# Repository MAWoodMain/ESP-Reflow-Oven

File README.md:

<!--
*** Thanks for checking out the Best-README-Template. If you have a suggestion
*** that would make this better, please fork the repo and create a pull request
*** or simply open an issue with the tag "enhancement".
*** Thanks again! Now go create something AMAZING! :D
***
***
***
*** To avoid retyping too much info. Do a search and replace for the following:
*** github_username, repo_name, twitter_handle, email, project_title, project_description
-->

<!--
*** This readme is based on the template from this github project
*** https://github.com/othneildrew/Best-README-Template
-->

<!-- PROJECT SHIELDS -->
<!--
*** I'm using markdown "reference style" links for readability.
*** Reference links are enclosed in brackets [ ] instead of parentheses ( ).
*** See the bottom of this document for the declaration of the reference variables
*** for contributors-url, forks-url, etc. This is an optional, concise syntax you may use.
*** https://www.markdownguide.org/basic-syntax/#reference-style-links
-->

<br />
<p align="center">

  <h3 align="center">ESP Reflow Oven</h3>

  <p align="center">
    A retro fit of a Lidl middle aisle mini oven into a home reflow oven
  </p>
</p>

<!-- TABLE OF CONTENTS -->
<details open="open">
  <summary><h2 style="display: inline-block">Table of Contents</h2></summary>
  <ol>
    <li>
      <a href="#about-the-project">About The Project</a>
      <ul>
        <li><a href="#objectives">Objectives</a></li>
        <li><a href="#component-selection">Component Selection</a></li>
      </ul>
    </li>
    <li>
      <a href="#the-build">The Build</a>
      <ul>
        <li><a href="#components">Components</a></li>
        <li><a href="#assembly">Assembly</a></li>
      </ul>
    </li>
    <li><a href="#the-final-product">The Final Product</a></li>
    <li><a href="#reflections">Reflections</a></li>
    <li><a href="#license">License</a></li>
  </ol>
</details>

<!-- ABOUT THE PROJECT -->
## About The Project
This project came about on a friday night trip to lidl in the UKs second lockdown. I spotted that lidl were selling mini ovens in the middle aisle for a meagre £25 (~$35), having seen many online creators doing their own homemade reflow ovens based on similar toaster ovens I though it would be a worthy weekend project.  
Naturally after getting home from lidl and putting away all the chilled and frozen foods I went straight into a teardown to see how this thing was put together, the original oven had 3 dials on the front:
* Temperature
* Mode (top/bottom/both elements)
* Timer

Under the hood there was practically nothing just a large void in the case with a few wires going to the elements, the temperature control was a simple bimetallic strip temeperature control which seems to operate based on the temperature in the chamber next to the oven? Not sure how that could even work properly, either way its going into the bin. Similar story for the mode switch, it just switches in and out elements based on the selection, this will not be required either.

After they were removed I was left with the mains input going through a thermal fuse and into a timer switch, I will keep the timer switch to I can set an automatic off when using the unit under computer control. Also this timer switch makes a rather satisfying ding sound when it turns off, I would hate to lose such an important feature...

<!-- OBJECTIVES -->
### Objectives
Had only a few key objectives when I started this project:

* All the mechanical components should be 3D printable using FDM technology.

* I wanted to utilise ESPHome as I have been following some creators project using it, and I was keen to give it a go.

* I wanted the SMT components on the PCB to be assembled by JLC assembly, I know this one sounds a bit weird given I am constructing a reflow oven, but it honestly is often cheaper to have components assembled at JLCPCB rather than ordering them, paying shipping for both PCBs and components then organising paste and a stencil. This oven if for when I have to use components not available for this service and for special cases.

* I needed the oven to follow a simple reflow curve, doesn't need to be prefect but it must work for basic board with normal components.

* I also wanted to try out a Nextion display as I had also seen a few videos by [Vaclav Chaloupka](https://www.youtube.com/user/bruxy70) making some cool home assistant home control panels using the modules.

* Finally I wanted to keep all the original products safety features in place so I don't create a major fire hazard.

<!-- COMPONENT SELECTION -->
### Component Selection

I knew this project would involve working with mains electricity so I made sure to choose components with recognisable approvals and safety certifications for the mains side of the electronics. For that reason I chose a [meanwell isolated AC to DC converter](https://www.meanwell.com/Upload/PDF/IRM-05/IRM-05-SPEC.PDF) to power the low voltage side of the electronics.

The heating elements were tested and found to draw around 600 Watts each which in the UK is around 2.5-3 Amps, the switching component selected for this load was a 5 Amp solid state relay. Specifically I made sure to select a zero crossing SSR as with resistive loads it is better for the powerline quality in the house as it avoids harsh mid phase loading. A [CX240D5](http://www.crydom.com/en/products/catalog/cx-series-ac-pcb-mount.pdf) was used as it was easily available and has approvals several reputable approvals (UL, CSA and CE).

A supplementary on board fuse holder and fuse was included in the design just in case the plug fuse is especially slow or overrated.

The low voltage side will be an ESP32, some thermocouple inputs and a DC output to allow for a fan in the future if required to cool the electronics.

For the thermocouple inputs I have very few ICs to choose from as JLC Assembly did not seem to have many available, I settled on the [MAX31855](https://datasheets.maximintegrated.com/en/ds/MAX31855.pdf) which includes cold junction compensation and requires no external components to work aside from basic decoupling. It uses SPI to send data back to the MCU, it has no settings to configure and does not support receiving data over SPI.

The fan output is a 5V power output which consists of a P-Channel MOSFET and a NPN drive transistor for the gate. This output can only support about 0.5A output as the meanwell power supply is only rated for 1A and the ESP32 required 0.5A.

Below is the 3D model of the PCB in the Kicad 3D viewer:

<!-- THE BUILD -->
## The Build

<!-- COMPONENTS -->
### Components

In addition to the assembled PCB discussed above and the 3D printed parts, a few extra components are required:
* 1 x u.FL to SMA pig tail to allow for an external antenna for the WiFi.
* 1 x SMA 2.4 GHz antenna
* 1 x USB to UART module (3.3V logic) to program the ESP and Nextion display
* 1x Nextion NX4832K035 display module
* 1x Custom cable to connect the nextion display to the PCB (JST-PH)
* 2x bead K type thermocouples
* Optional 1x high mass K type thermocouple for chamber air temperature

<!-- ASSEMBLY -->
### Assembly
The PCBs arrived SMT complete from JLCPCB, the THT components were hand soldered in to finish the PCBA off.
At this point it is worth getting the firmware uploaded into the ESP32, after the first firmware is loaded OTA updating is trivial using the ESPHome home assistant plugin.

It is also worth preparing the Nextion display module, I uploaded the firmware to the display using a USB to UART module and the nextion editor software.

As discussed in the project intro the original mode and temperature knobs were removed. 
Next some stand offs were mounted in the space next to the heating chamber to affix the PCB to.
The PCB was mounted and custom cables were crimped to connect up the mains input and heating elements.
Some holes were drilled to allow the thermocouples into the heated chamber one on the top of the right side and one on the bottom.

A hole was drilled for the SMA connector on the top and the u.FL end was plugged into the ESP32 module.

Next the 3D printed LCD mount was screwed into the front panel using the original self tapping screws which held the old controls on. The LCD was itself screwed into the mount using M3x10mm pan head bolts and the cable was run back to the main PCB. The LCD cover was pressed on to finish off the front. I discovered you must take care pressing this cover on as if you press it on too far it triggers the resistive touch screen on the nextion module.

Below is a photo of the electronics compartment, please don't judge the wire runs too heavily as it has been improved since.

Once the assembly was complete the PIDs loops require tuning so I attached the top and bottom thermocouples to a blank PCB and ran the auto tune routine for both the top and bottom PID control loops.
These values were saved into the ESPHome YAML so they persist though reboot.

<!-- THE FINAL PRODUCT -->
## The Final Product

<!-- REFLECTIONS -->
## Reflections

I am happy with the final product I think the outside looks very clean and the interface is simple and intuitive.
There are a few issues I ran into during this project:
* Two PID loops, since I went with independent top and bottom heat controls I have two PID loops for the top and bottom systems but since these two systems are used simultaneously they are not independent closed loop systems. The issue with this is that the PID settings do not account properly the other loop existing and thus tend to overshoot the set temperature when they are used together. For reflow I have not found a 5 degree overshoot to be a problem but for some use cases I could see it being an issue. I would propose two possible solutions: You could either combine the two elements and control them as a single large element in a single PID loop or you could use a more sophisticated control system which accounted for the second elements influence.

* Dependence on Home assistant, in the way I am currently controlling it the oven relys on HASS to orchastrate the reflow cycle, if the connection to HASS is lost the oven could be left on at the set temperature for too long. Also it means if HASS is unavailable the cycle button does not work properly. This could be resolved by hard coding the cycle into the ESPHome config, but I have not done this yet.

* Cost, this project was started because of the cheapness of the oven but untimately its cost mostly came in the PCBA price. The total price of the PCB was around £17 for the PCBs from JLC (part assembled) and around £35 of THT parts from Farnell for a total cost of £52 (parts) + £25 (oven) = £77 (~$105). I don't feel I over spent given the capability of this oven but it is slightly more then I though it would cost. The main cost issue was in the farnell parts but this was caused by the safe main voltage components, so it is likely unavoidable.

<!-- LICENSE -->
## License

Distributed under the MIT License. See `LICENSE` for more information.

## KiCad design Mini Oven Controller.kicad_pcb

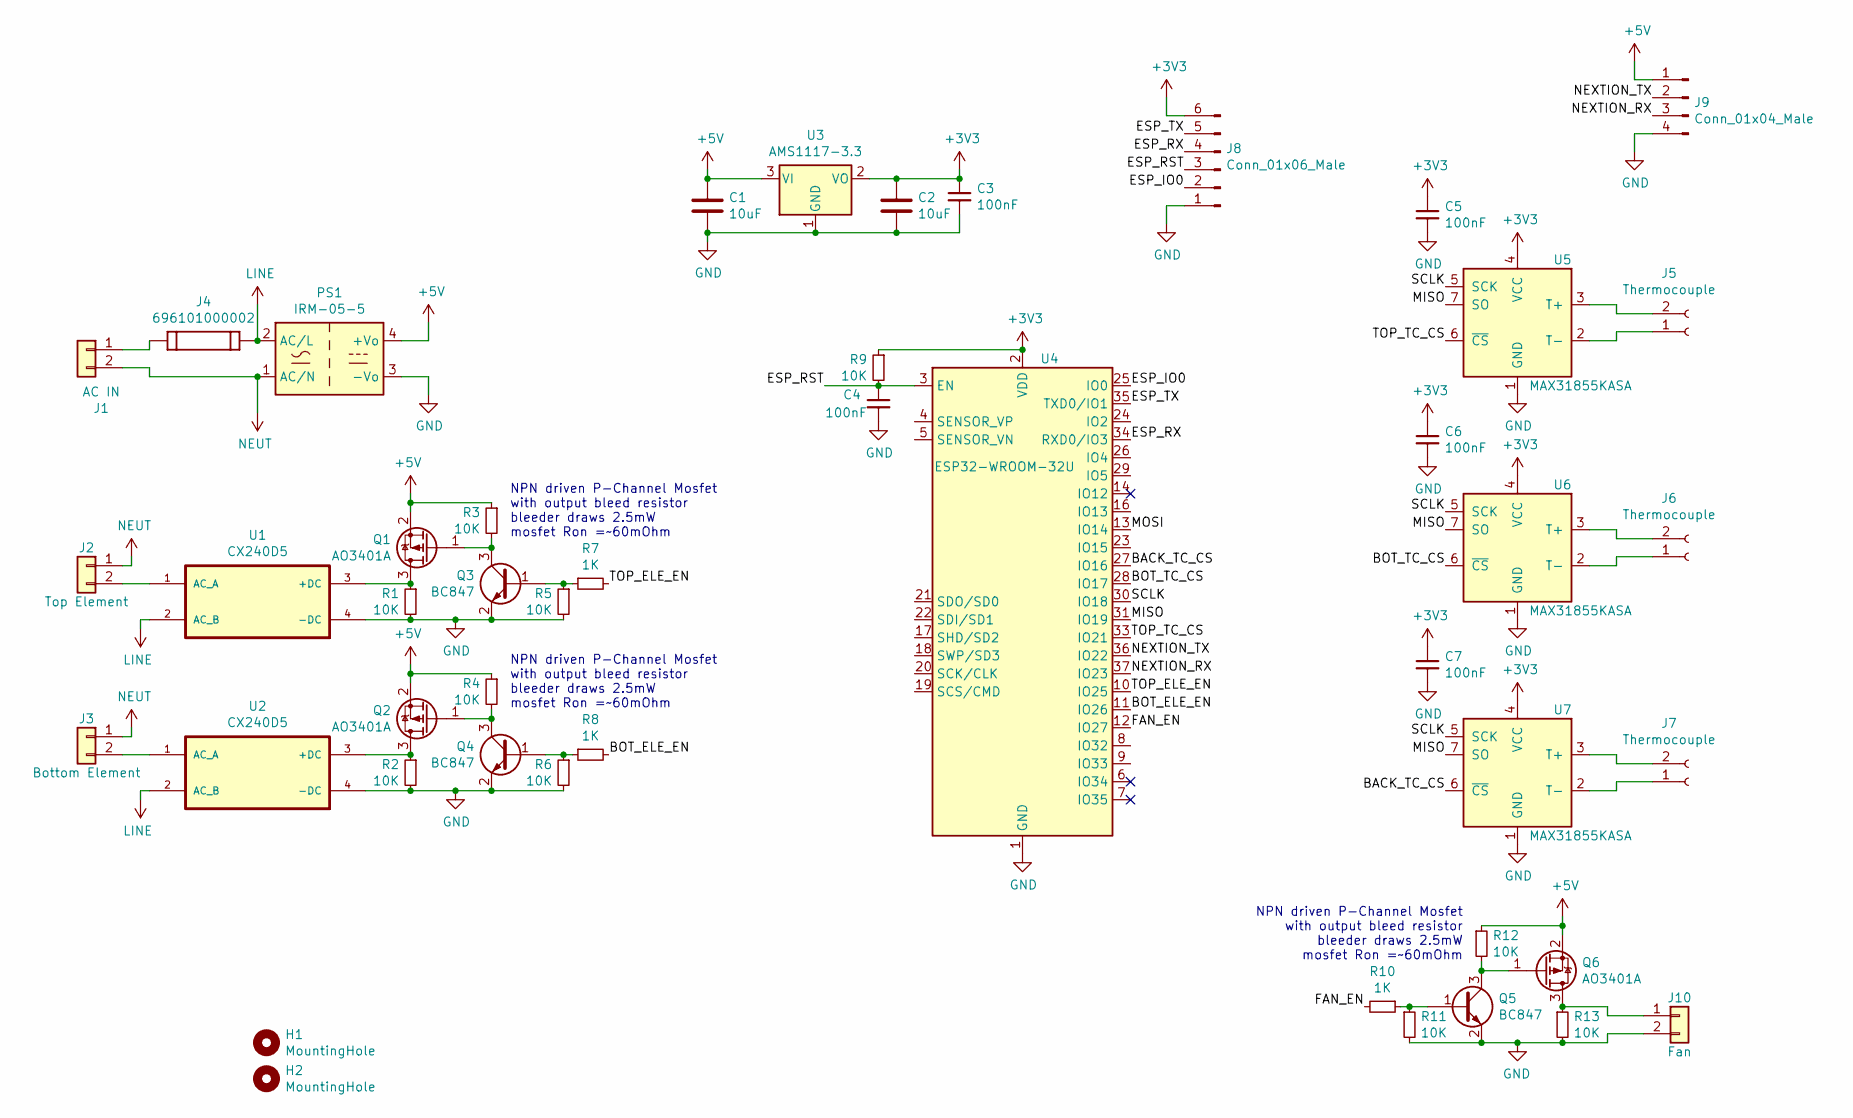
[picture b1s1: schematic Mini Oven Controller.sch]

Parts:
C1, C2: 10uF; C_0805_2012Metric; LCSC Part C15850
C3, C4, C5, C6, C7: 100nF; C_0603_1608Metric; LCSC Part C14663
H1, H2: MountingHole; MountingHole_3.2mm_M3; JLCPCB BOM 0
J1: AC IN; TerminalBlock_Phoenix_MKDS-3-2-5.08_1x02_P5.08mm_Horizontal; JLCPCB BOM 0
J2: Top Element; TerminalBlock_Phoenix_MKDS-3-2-5.08_1x02_P5.08mm_Horizontal; JLCPCB BOM 0
J3: Bottom Element; TerminalBlock_Phoenix_MKDS-3-2-5.08_1x02_P5.08mm_Horizontal; JLCPCB BOM 0
J4: 696101000002; PART-NUMBER 696101000002
J5, J6, J7: Thermocouple; IM-K-PCB; JLCPCB BOM 0
J8: Conn_01x06_Male; JST_PH_B6B-PH-K_1x06_P2.00mm_Vertical; JLCPCB BOM 0
J9: Conn_01x04_Male; JST_PH_B4B-PH-K_1x04_P2.00mm_Vertical; JLCPCB BOM 0
J10: Fan; TerminalBlock_Phoenix_MKDS-3-2-5.08_1x02_P5.08mm_Horizontal; JLCPCB BOM 0
PS1: IRM-05-5; Converter_ACDC_MeanWell_IRM-05-xx_THT; JLCPCB BOM 0
Q1, Q2, Q6: AO3401A; SOT-23; LCSC Part C15127
Q3, Q4, Q5: BC847; SOT-23; LCSC Part C426568
R1, R2, R3, R4, R5, R6, R9, R11, R12, R13: 10K; R_0603_1608Metric; LCSC Part C25804
R7, R8, R10: 1K; R_0603_1608Metric; LCSC Part C21190
U1, U2: CX240D5; CRYDOM_CX240D5; JLCPCB BOM 0
U3: AMS1117-3.3; SOT-223-3_TabPin2; LCSC Part C6186
U4: ESP32-WROOM-32U; LCSC Part C328062
U5, U6, U7: MAX31855KASA; SOIC-8_3.9x4.9mm_P1.27mm; LCSC Part C52028

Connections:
+3V3: C2.1, C3.1, C5.1, C6.1, C7.1, J8.6, R9.1, U3.2 (VO), U4.2 (VDD), U5.4 (VCC), U6.4 (VCC), U7.4 (VCC)
+5V: C1.1, J9.1, PS1.4 (+Vo), Q1.2 (S), Q2.2 (S), Q6.2 (S), R3.1, R4.1, R12.1, U3.3 (VI)
/BACK_TC_CS: U4.27 (IO16), U7.6 (~CS~)
/BOT_ELE_EN: R8.2, U4.11 (IO26)
/BOT_TC_CS: U4.28 (IO17), U6.6 (~CS~)
/ESP_IO0: J8.2, U4.25 (IO0)
/ESP_RST: C4.1, J8.3, R9.2, U4.3 (EN)
/ESP_RX: J8.4, U4.34 (RXD0/IO3)
/ESP_TX: J8.5, U4.35 (TXD0/IO1)
/FAN_EN: R10.2, U4.12 (IO27)
/MISO: U4.31 (IO19), U5.7 (SO), U6.7 (SO), U7.7 (SO)
/MOSI: U4.13 (IO14)
/NEXTION_RX: J9.3, U4.37 (IO23)
/NEXTION_TX: J9.2, U4.36 (IO22)
/SCLK: U4.30 (IO18), U5.5 (SCK), U6.5 (SCK), U7.5 (SCK)
/TOP_ELE_EN: R7.2, U4.10 (IO25)
/TOP_TC_CS: U4.33 (IO21), U5.6 (~CS~)
GND: C1.2, C2.2, C3.2, C4.2, C5.2, C6.2, C7.2, J8.1, J9.4, J10.2, PS1.3 (-Vo), Q3.2 (E), Q4.2 (E), Q5.2 (E), R1.2, R2.2, R5.2, R6.2, R11.2, R13.2, U1.4 (-DC), U2.4 (-DC), U3.1 (GND), U4.1 (GND), U4.15 (GND), U4.38 (GND), U4.39 (GND), U5.1 (GND), U6.1 (GND), U7.1 (GND)
LINE: J4.2, PS1.2 (AC/L), U1.2 (AC_B), U2.2 (AC_B)
NEUT: J1.2, J2.1, J3.1, PS1.1 (AC/N)
unnamed: J1.1, J4.1
unnamed: J2.2, U1.1 (AC_A)
unnamed: J3.2, U2.1 (AC_A)
unnamed: J5.1, U5.2 (T-)
unnamed: J5.2, U5.3 (T+)
unnamed: J6.1, U6.2 (T-)
unnamed: J6.2, U6.3 (T+)
unnamed: J7.1, U7.2 (T-)
unnamed: J7.2, U7.3 (T+)
unnamed: J10.1, Q6.3 (D), R13.1
unnamed: Q1.1 (G), Q3.3 (C), R3.2
unnamed: Q1.3 (D), R1.1, U1.3 (+DC)
unnamed: Q2.1 (G), Q4.3 (C), R4.2
unnamed: Q2.3 (D), R2.1, U2.3 (+DC)
unnamed: Q3.1 (B), R5.1, R7.1
unnamed: Q4.1 (B), R6.1, R8.1
unnamed: Q5.1 (B), R10.1, R11.1
unnamed: Q5.3 (C), Q6.1 (G), R12.2

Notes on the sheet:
NPN driven P-Channel Mosfet with output bleed resistor bleeder draws 2.5mW mosfet Ron =~~60mOhm

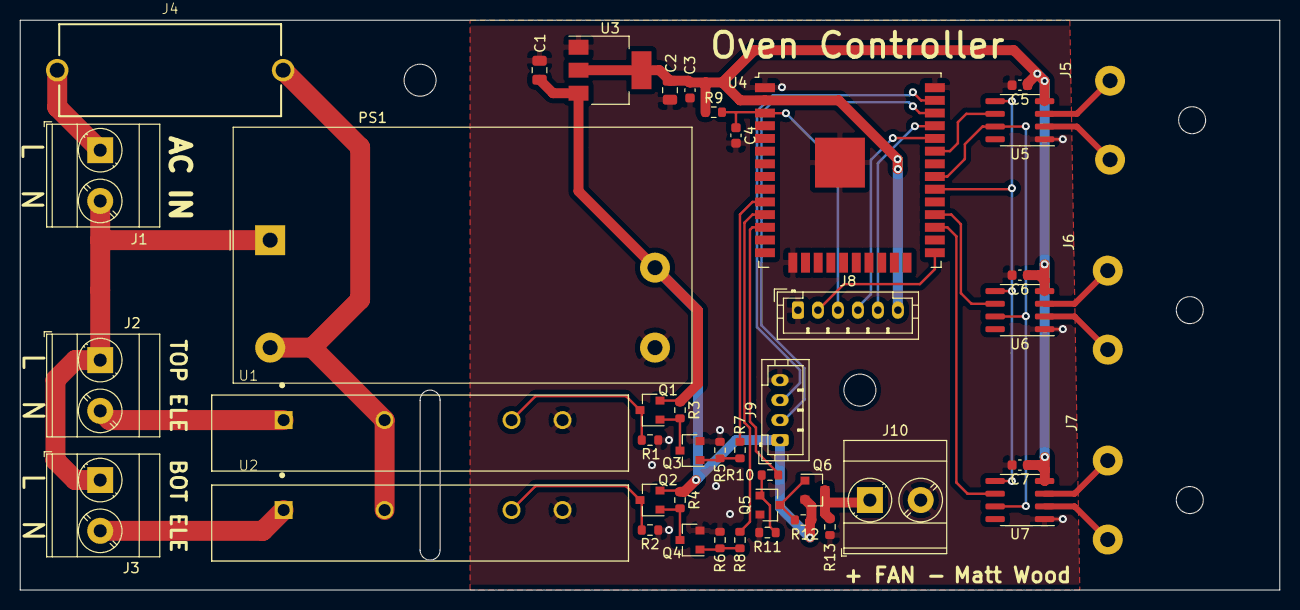
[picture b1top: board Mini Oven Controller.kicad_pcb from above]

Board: 2 copper layers, 126.0 x 57.0 mm, 46 parts (0 on the bottom side), 37 nets.

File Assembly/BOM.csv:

Comment,Designator,Footprint,LCSC Part #
10uF Unpolarized capacitor,"C1,C2",C_0805_2012Metric,C15850
"100nF Unpolarized capacitor, small symbol","C3,C4,C5,C6,C7",C_0603_1608Metric,C14663
696101000002 ,J4,696101000002,
"AO3401A -4.0A Id, -30V Vds, P-Channel MOSFET, SOT-23","Q1,Q2,Q6",SOT-23,C15127
"BC847 0.1A Ic, 45V Vce, NPN Transistor, SOT-23","Q3,Q4,Q5",SOT-23,C426568
"10K Resistor, small symbol","R1,R2,R3,R4,R5,R6,R9,R11,R12,R13",R_0603_1608Metric,C25804
"1K Resistor, small symbol","R7,R8,R10",R_0603_1608Metric,C21190
"AMS1117-3.3 1A Low Dropout regulator, positive, 3.3V fixed output, SOT-223",U3,SOT-223-3_TabPin2,C6186
"ESP32-WROOM-32U RF Module, ESP32-D0WD SoC, Wi-Fi 802.11b/g/n, Bluetooth, BLE, 32-bit, 2.7-3.6V, external antenna, SMD",U4,ESP32-WROOM-32U,C328062
"MAX31855KASA Cold Junction K-type Termocouple Interface, SPI, SO8","U5,U6,U7",SOIC-8_3.9x4.9mm_P1.27mm,C52028

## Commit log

2021-02-06 Initial upload of project files, PCB updated to correct prototype mistake. ESP home YAML file and nextion display config included.
2021-02-06 saved and exited pcbnew
2021-02-06 Uploading photos of finished unit
2021-02-06 Added in 3D printed part files in F3D, STEP and STL format
2021-02-06 Create README.md
    Created the readme templated based on https://github.com/othneildrew/Best-README-Template/blob/master/BLANK_README.md
2021-02-06 Cropped Photo
2021-02-06 Added a PDF schematic
2021-02-06 Create LICENSE
2021-02-06 Added content to readme
